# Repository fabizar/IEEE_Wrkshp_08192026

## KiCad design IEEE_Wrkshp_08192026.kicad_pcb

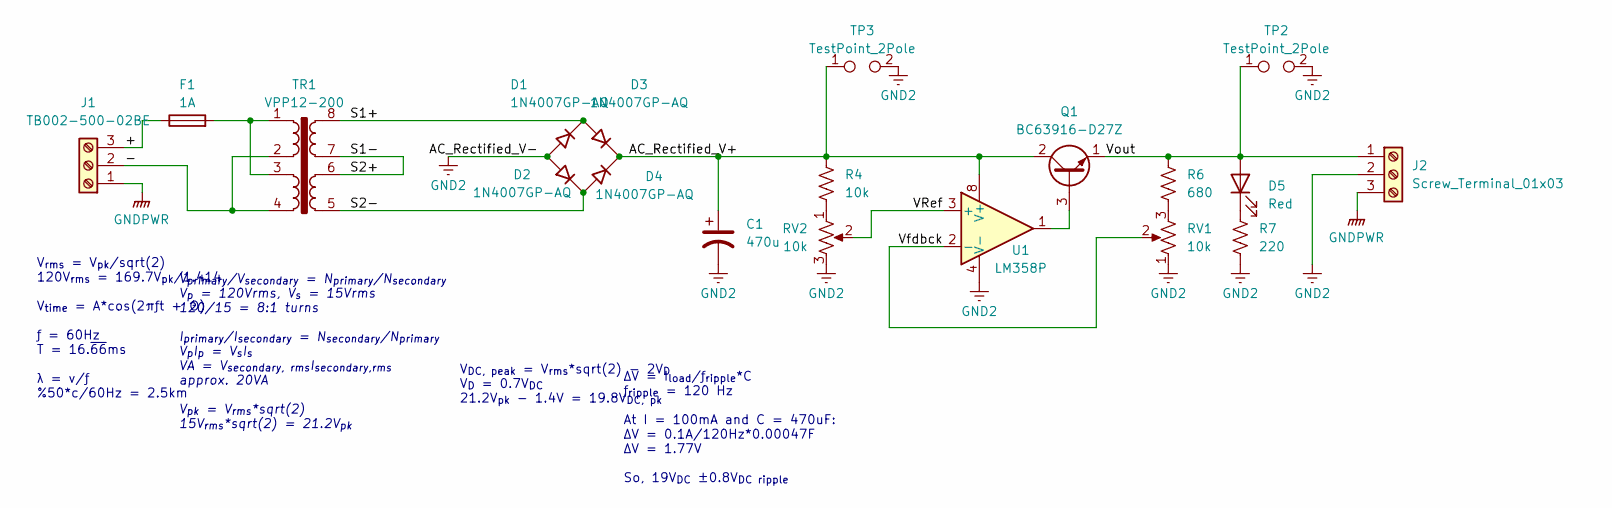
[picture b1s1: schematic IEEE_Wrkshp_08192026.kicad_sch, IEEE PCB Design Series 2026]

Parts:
C1: 470u; CP_Radial_D8.0mm_P3.50mm
D1, D2, D3, D4: 1N4007GP-AQ; D_DO-35_SOD27_P7.62mm_Horizontal
D5: Red; LED_D5.0mm
F1: 1A; Fuseholder_Clip-5x20mm_Keystone_3517_Inline_P23.11x6.76mm_D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
J1: TB002-500-02BE; TerminalBlock_Phoenix_MKDS-1,5-3_1x03_P5.00mm_Horizontal
J2: Screw_Terminal_01x03; TerminalBlock_Phoenix_MKDS-1,5-3_1x03_P5.00mm_Horizontal
Q1: BC63916-D27Z; TO-92_Inline_Wide
R4: 10k; R_Axial_DIN0309_L9.0mm_D3.2mm_P12.70mm_Horizontal
R6: 680; R_Axial_DIN0309_L9.0mm_D3.2mm_P12.70mm_Horizontal
R7: 220; R_Axial_DIN0309_L9.0mm_D3.2mm_P12.70mm_Horizontal
RV1, RV2: 10k; Potentiometer_Runtron_RM-063_Horizontal
TP2, TP3: TestPoint_2Pole; TestPoint_2Pads_Pitch2.54mm_Drill0.8mm
TR1: VPP12-200; XFMR_VPP12-200
U1: LM358P; DIP-8_W7.62mm_LongPads

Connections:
/+: F1.1, J1.3
/-: J1.2, TR1.2, TR1.4
/AC_Rectified_V+: C1.1, D3.1 (K), D4.1 (K), Q1.2 (C), R4.1, TP3.1, U1.8 (V+)
/S1+: D1.1 (K), D3.2 (A), TR1.8
/S1-: TR1.6, TR1.7
/S2-: D2.1 (K), D4.2 (A), TR1.5
/VRef: RV2.2, U1.3 (+)
/Vfdbck: RV1.2, U1.2 (-)
/Vout: D5.2 (A), J2.1, Q1.1 (E), R6.1, TP2.1
GND2: C1.2, D1.2 (A), D2.2 (A), J2.2, R7.2, RV1.1, RV2.3, TP2.2, TP3.2, U1.4 (V-)
GNDPWR: J1.1, J2.3
unnamed: D5.1 (K), R7.1
unnamed: F1.2, TR1.1, TR1.3
unnamed: Q1.3 (B), U1.1
unnamed: R4.2, RV2.1
unnamed: R6.2, RV1.3

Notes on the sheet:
V_{rms} = V_{pk}/sqrt(2) 120V_{rms} = 169.7V_{pk}/1.414 V_{time} = A*cos(2πƒt + Θ) ƒ = 60Hz T = 16.~{66}ms λ = v/ƒ %50*c/60Hz = 2.5km
V_{DC, peak} = V_{rms}*sqrt(2) - 2V_{D} V_{D} = 0.7V_{DC} 21.2V_{pk} - 1.4V = 19.8V_{DC, pk}
ΔV = I_{load}/ƒ_{ripple}*C ƒ_{ripple} = 120 Hz At I = 100mA and C = 470uF: ΔV = 0.1A/120Hz*0.00047F ΔV = 1.77V So, 19V_{DC} ±0.8V_{DC ripple}
V_{primary}/V_{secondary} = N_{primary}/N_{secondary} V_{p} = 120Vrms, V_{s} = 15Vrms 120/15 = 8:1 turns I_{primary}/I_{secondary} = N_{secondary}/N_{primary} V_{p}I_{p} = V_{s}I_{s} VA = V_{secondary, rms}I_{secondary,rms} approx. 20VA V_{pk} = V_{rms}*sqrt(2) 15V_{rms}*sqrt(2) = 21.2V_{pk}

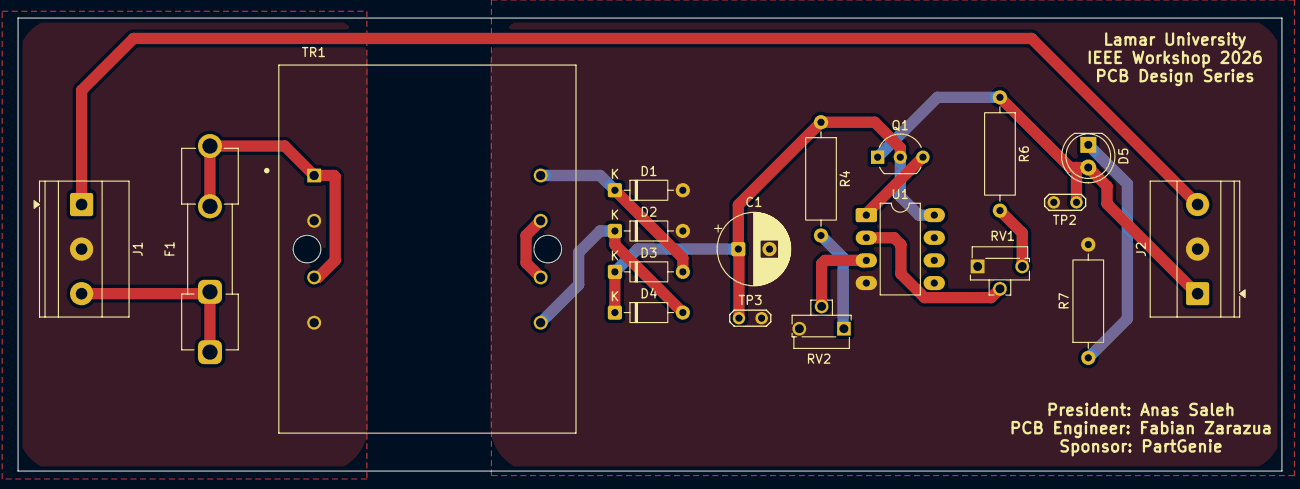
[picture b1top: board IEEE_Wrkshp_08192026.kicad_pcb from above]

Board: 2 copper layers, 141.7 x 50.8 mm, 19 parts (0 on the bottom side), 16 nets.
